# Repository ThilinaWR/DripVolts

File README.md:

# DripVolts
ME Group Project
"Harnessing the Power of Rainwater for Sustainable Electricity Generation"
We are developing an innovative system that converts the kinetic and potential energy of rainwater into electricity. By collecting and channeling rainwater through a micro-hydropower setup—such as turbines or piezoelectric surfaces—we aim to provide an eco-friendly, renewable source of energy. This solution is particularly suited for regions with high rainfall and can contribute to decentralized, off-grid power supply, enhancing energy access and sustainability.
 Youtube: https://www.youtube.com/channel/UCPZSMZEaV4SD8Ak0Q1TPr5A

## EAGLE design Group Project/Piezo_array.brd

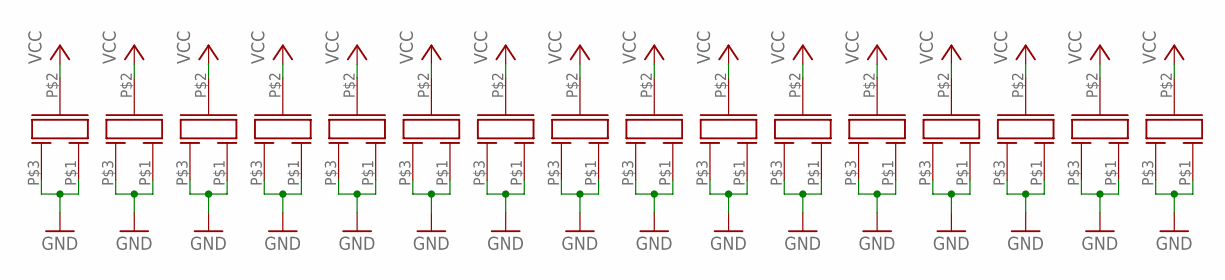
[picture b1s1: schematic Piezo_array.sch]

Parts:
U$2, U$3, U$4, U$5, U$6, U$7, U$8, U$17, U$18, U$19, U$20, U$21, U$22, U$23, U$24, U$25: PIEZO

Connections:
GND: U$2.P$1, U$2.P$3, U$3.P$1, U$3.P$3, U$4.P$1, U$4.P$3, U$5.P$1, U$5.P$3, U$6.P$1, U$6.P$3, U$7.P$1, U$7.P$3, U$8.P$1, U$8.P$3, U$17.P$1, U$17.P$3, U$18.P$1, U$18.P$3, U$19.P$1, U$19.P$3, U$20.P$1, U$20.P$3, U$21.P$1, U$21.P$3, U$22.P$1, U$22.P$3, U$23.P$1, U$23.P$3, U$24.P$1, U$24.P$3, U$25.P$1, U$25.P$3
VCC: U$2.P$2, U$3.P$2, U$4.P$2, U$5.P$2, U$6.P$2, U$7.P$2, U$8.P$2, U$17.P$2, U$18.P$2, U$19.P$2, U$20.P$2, U$21.P$2, U$22.P$2, U$23.P$2, U$24.P$2, U$25.P$2

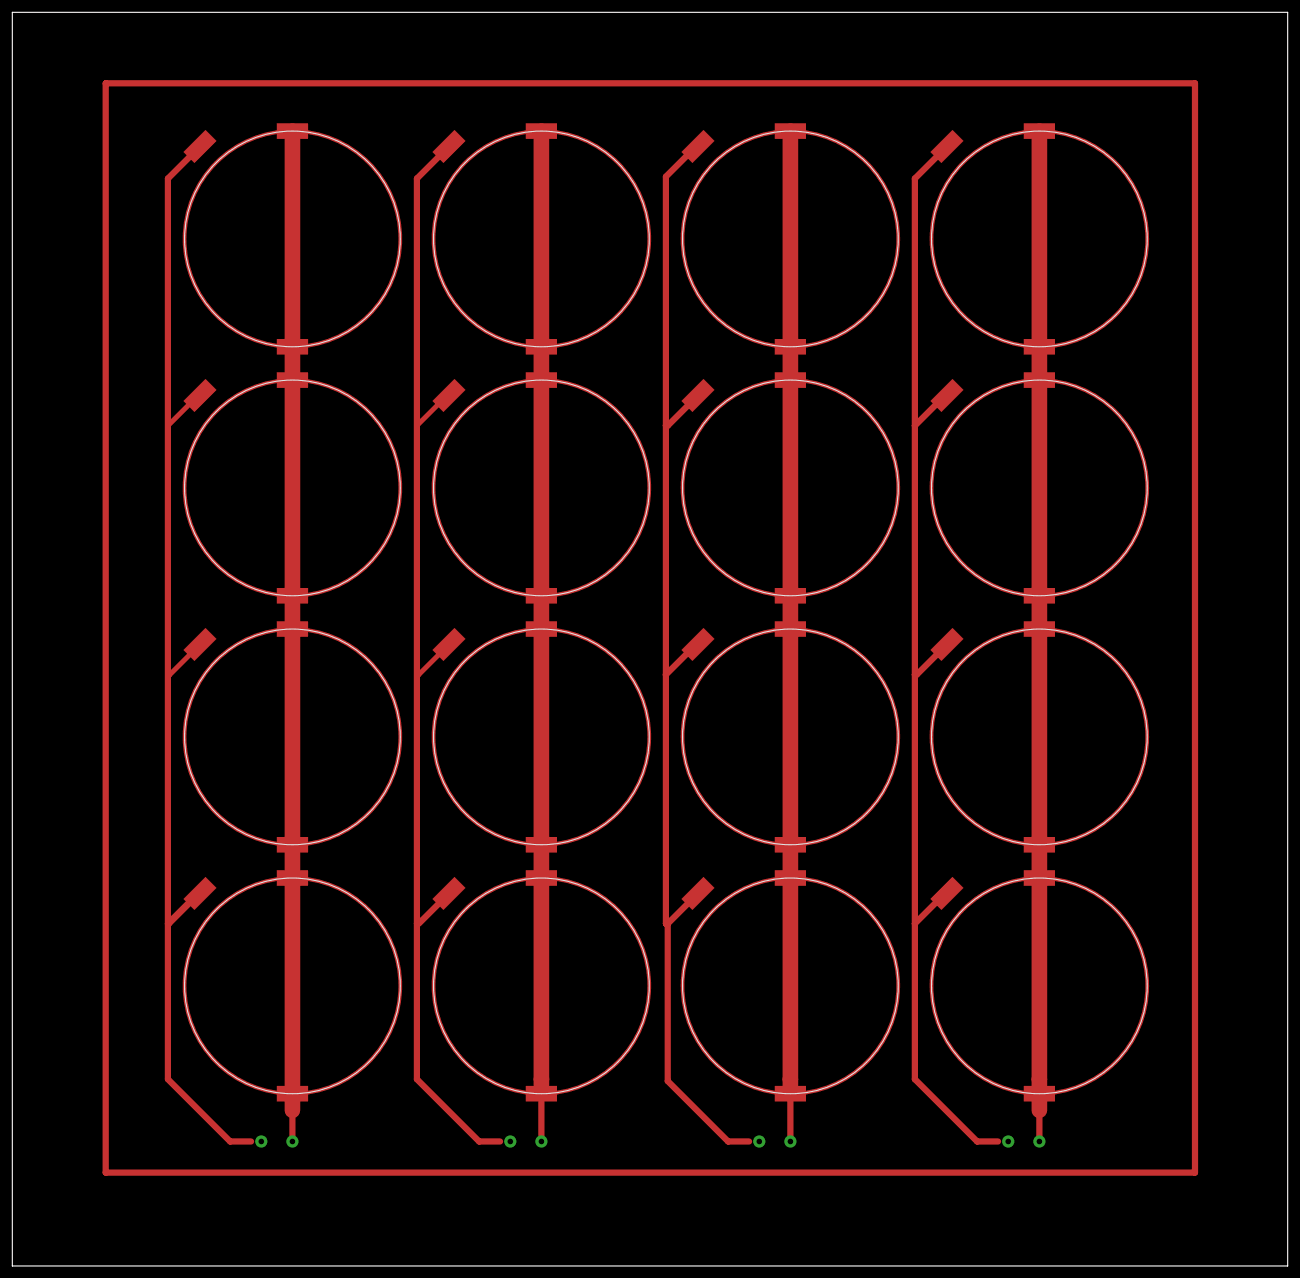
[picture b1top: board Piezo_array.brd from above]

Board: 2 copper layers, 206.9 x 203.4 mm, 16 parts (0 on the bottom side), 2 nets.

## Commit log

2025-05-22 Create Eagle_files
    PCB Designs
2025-06-23 Add files via upload
    schematics
2025-07-20 Add files via upload
    These are the Solidworks models of the cell.
2025-07-20 Add files via upload
    Naming convention of the cell and its parts
2025-07-20 Add files via upload
    Logo used by our group "DripVolts"
2025-12-17 Created using Colab
